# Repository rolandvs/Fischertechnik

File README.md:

# Fischertechnik Revisited

This repository holds my experiments with Fischertechnik.

Recently I got some old building blocks and accessoires. It is like reliving my youth. Today I can appreciate the powerfulness of the blocks much more and now I can also add things I like to it.

So now I started this repo. First thing was to create 3D printed blocks that can be used together with the original stuff. The purpose is not to duplicate it, but
be able to add small (electronics based) blocks w/ or w/o pogo pins, small PCB, having sensors and other stuff.

# 3D

In the 3D directory you will find two `NOT VERIFIED YET` blocks that serve as basis to build other blocks. The OpenSCAD source and a `.STL` can be found there.

No part has been printed yet to see if the measures are correct (lacking a 3D printer).

# KiCad

In the KiCad directory you will find projects that can be useful. Expect a sensor PCB that fits one of the 3D designs, H-bridge for the motors and interfaces to `STM32` and/or `BBC micro:bit`.

## Baustein_15_LED

Just for test and fun a dual LED PCB that can hold two different colors or the same colors and will light one or the other LED when a DC voltage is applied. When an AC voltage is applied they both will be on.

## Baustein_151_SENSOR

Re-purposing a _line follower optical sensor_ for use as a switch.

## H-Bridge micro:bit

Fischertechnik provides a micro:bit interface with two H-bridges [link](https://www.fischertechnik.biz/fischertechnik-education-starter-set-for-micro-bit). 

The contact points can fit a connector directly. For my use it is to expensive to buy the kit, especially while having the parts here in the junkbox.

This project is inspired by the work of [Didacta's Education Projects](http://www.didacta.hr/)

Currently made:
- Symbols for the micro:bit connector
- Symbol for the 2.5mm plugs (also used by Märklin)

Starting to add more interfaces... `WORK IN PROGRESS`

## H-Bridge variants

### Tibbo Box Module

A nice Linux platform with a casing that allows modules. `WORK IN PROGRESS`

### SMD

Also started designing with a nice Toshiba IC that saves some room (SMD). See KiCad project...

## STM32 Controller

Ideation phase...

`WORK IN PROGRESS`

# Projects

In this section some projects will be documented.

`WORK IN PROGRESS`

## Elevator

The elevator is a project that has two multi-floor elevators where the users can press a button per floor. Depending on the traffic, the correct elevator is selected to either move up or down, with its intent to do this ASAP.

Go to [Elevator Project](Projects/Elevator/README.md) - `WORK IN PROGRESS`

## Crane

A crane lifting a load and bring it to its specific location. It involves using Fuzzy Logic to compensate for the pendulum effect.

Go to [Crane Project](Projects/Crane/README.md) - `WORK IN PROGRESS`

# Other Sources

[Fischertechnikclub Nederland](https://docs.fischertechnikclub.nl/) </br>

[Fischertechnik Database](https://ftdb.eu/) </br>

** Very nice website, good mix of STEM, IoT and Fischertechnik!** Nice magazines for downloading!!

[Tech Ecke](https://www.tech-ecke.de/index_quereinstieg.htm?/basteleien/fischertechnik.htm)

_____
_____
Copyright (c)2026 by Roland van Straten. All Rights Reserved. Commercial in Confidence.

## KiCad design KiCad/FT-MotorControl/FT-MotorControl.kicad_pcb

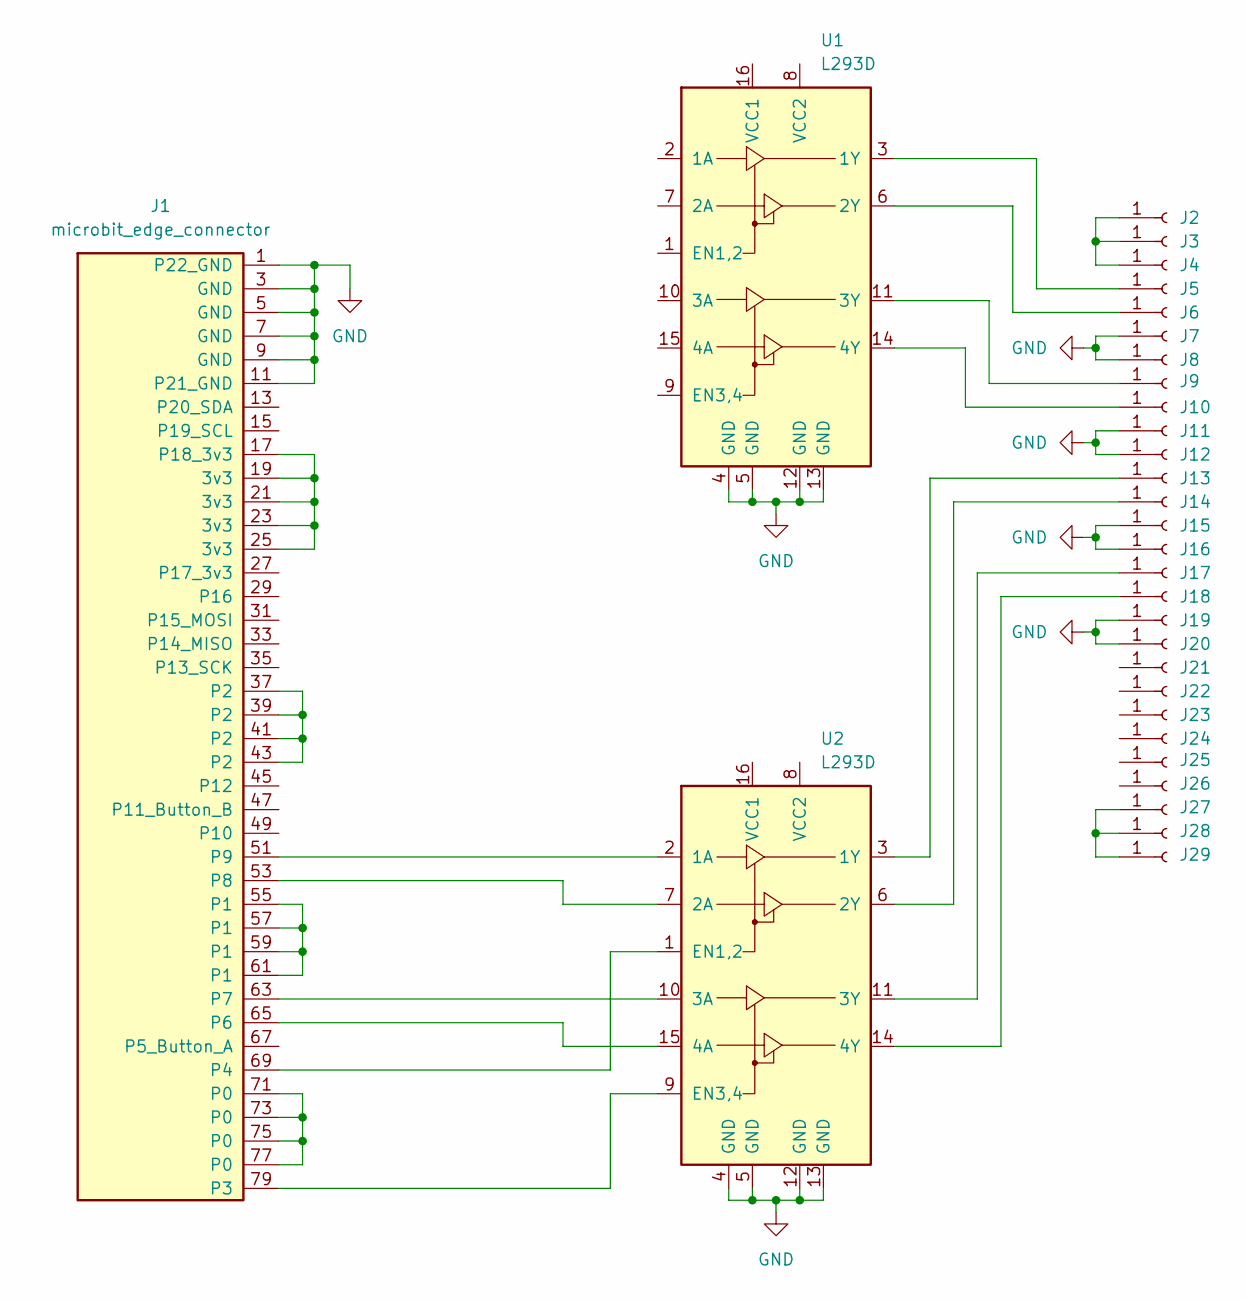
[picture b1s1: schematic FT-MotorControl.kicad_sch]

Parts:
J1: microbit_edge_connector; 4UCON_17909_02x401.27mm_Vertical
J2, J3, J4, J5, J6, J7, J8, J9, J10, J11, J12, J13, J14, J15, J16, J17, J18, J19, J20, J21, J22, J23, J24, J25, J26, J27, J28, J29: Conn_01x01_Socket; Marklin_7132_7135_Plug_PressFit
U1, U2: L293D; DIP-16_W7.62mm

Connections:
GND: J1.1 (P22_GND), J1.3 (GND), J1.5 (GND), J1.7 (GND), J1.9 (GND), J1.11 (P21_GND), J7.1 (Pin_1_1), J8.1 (Pin_1_1), J11.1 (Pin_1_1), J12.1 (Pin_1_1), J15.1 (Pin_1_1), J16.1 (Pin_1_1), J19.1 (Pin_1_1), J20.1 (Pin_1_1), U1.4 (GND), U1.5 (GND), U1.12 (GND), U1.13 (GND), U2.4 (GND), U2.5 (GND), U2.12 (GND), U2.13 (GND)
unnamed: J1.71 (P0), J1.73 (P0), J1.75 (P0), J1.77 (P0)
unnamed: J1.55 (P1), J1.57 (P1), J1.59 (P1), J1.61 (P1)
unnamed: J1.37 (P2), J1.39 (P2), J1.41 (P2), J1.43 (P2)
unnamed: J1.79 (P3), U2.9 (EN3,4)
unnamed: J1.69 (P4), U2.1 (EN1,2)
unnamed: J1.65 (P6), U2.15 (4A)
unnamed: J1.63 (P7), U2.10 (3A)
unnamed: J1.53 (P8), U2.7 (2A)
unnamed: J1.51 (P9), U2.2 (1A)
unnamed: J1.17 (P18_3v3), J1.19 (3v3), J1.21 (3v3), J1.23 (3v3), J1.25 (3v3)
unnamed: J2.1 (Pin_1_1), J3.1 (Pin_1_1), J4.1 (Pin_1_1)
unnamed: J5.1 (Pin_1_1), U1.3 (1Y)
unnamed: J6.1 (Pin_1_1), U1.6 (2Y)
unnamed: J9.1 (Pin_1_1), U1.11 (3Y)
unnamed: J10.1 (Pin_1_1), U1.14 (4Y)
unnamed: J13.1 (Pin_1_1), U2.3 (1Y)
unnamed: J14.1 (Pin_1_1), U2.6 (2Y)
unnamed: J17.1 (Pin_1_1), U2.11 (3Y)
unnamed: J18.1 (Pin_1_1), U2.14 (4Y)
unnamed: J27.1 (Pin_1_1), J28.1 (Pin_1_1), J29.1 (Pin_1_1)

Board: 2 copper layers, 31 parts (0 on the bottom side), 21 nets, no tracks yet.

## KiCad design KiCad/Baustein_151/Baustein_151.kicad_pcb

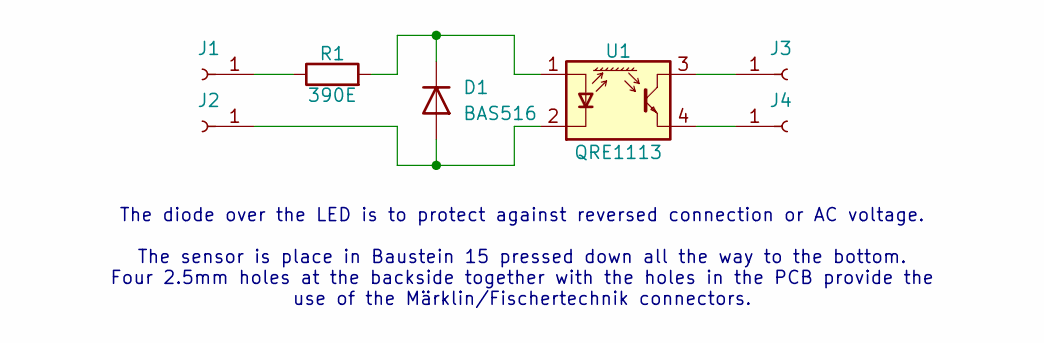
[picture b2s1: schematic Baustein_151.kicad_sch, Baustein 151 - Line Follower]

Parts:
D1: BAS516; D_SOD-523
J1, J2, J3, J4: Conn_01x01_Socket; Marklin_7132_7135_Plug_PressFit
R1: 390E; R_0603_1608Metric_Pad0.98x0.95mm_HandSolder
U1: QRE1113; OnSemi_CASE100AQ

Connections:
unnamed: D1.2 (A), J2.1 (Pin_1_1), U1.2 (K)
unnamed: D1.1 (K), R1.2, U1.1 (A)
unnamed: J1.1 (Pin_1_1), R1.1
unnamed: J3.1 (Pin_1_1), U1.3
unnamed: J4.1 (Pin_1_1), U1.4

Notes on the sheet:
The diode over the LED is to protect against reversed connection or AC voltage. The sensor is place in Baustein 15 pressed down all the way to the bottom. Four 2.5mm holes at the backside together with the holes in the PCB provide the use of the Märklin/Fischertechnik connectors.

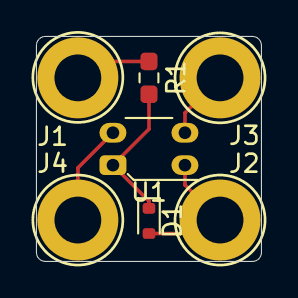
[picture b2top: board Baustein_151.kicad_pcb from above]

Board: 2 copper layers, 12.5 x 12.5 mm, 7 parts (0 on the bottom side), 5 nets.

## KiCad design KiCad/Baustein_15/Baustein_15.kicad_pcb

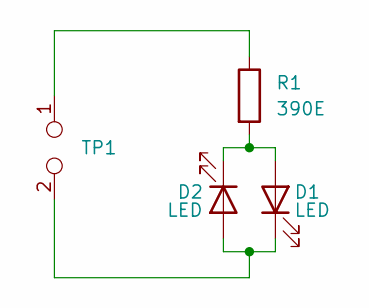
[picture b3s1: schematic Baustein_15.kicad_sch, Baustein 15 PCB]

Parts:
D1, D2: LED; LED_0603_1608Metric_Pad1.05x0.95mm_HandSolder
R1: 390E; R_0603_1608Metric_Pad0.98x0.95mm_HandSolder
TP1: TestPoint_2Pole; TestPoint_2Pads_Pitch2.54mm_Drill0.8mm

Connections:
unnamed: D1.2 (A), D2.1 (K), R1.2
unnamed: D1.1 (K), D2.2 (A), TP1.2
unnamed: R1.1, TP1.1

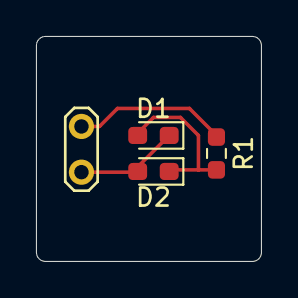
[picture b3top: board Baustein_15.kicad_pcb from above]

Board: 2 copper layers, 12.5 x 12.5 mm, 4 parts (0 on the bottom side), 3 nets.

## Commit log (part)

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2026-05-04 Basic information added
2026-05-04 Fix image paths in README.md
    Updated image paths in README for correct referencing.
2026-05-04 Fix image paths in README.md
    Updated image paths in README for consistency.
2026-05-05 Exclude some files/folders
2026-05-05 Some local file suppression
2026-05-05 Added some more FT products
2026-05-05 Component Datasheets added
2026-05-05 Fix spelling errors in README.md
    Corrected spelling errors in README content.
2026-05-05 Add preview H-bridge interface
2026-05-05 Add updated readme
2026-05-05 Add library for 2.5mm plug receptable
2026-05-08 Suppress some KiCad history
2026-05-08 Add datasheet AD converter
2026-05-08 Added crane info
2026-05-08 Add elevator information
2026-05-22 Added concept of H-Bridge for 4 motors
2026-05-22 Added an updated picture of the elevator(s)
2026-05-22 Added a small block with a line follower optic sensor
2026-05-22 Added updates to the project
2026-05-25 add marklin pressfit 2.5mm symbol/footprint
2026-05-25 add FT-MotorControl project
2026-05-25 add connector Marklin, soldering version (of little use)
2026-05-25 add micro:bit motor control variant/ micro:bit connector
2026-05-25 suppress backup file directories
2026-06-28 Two dedicated magazines added
